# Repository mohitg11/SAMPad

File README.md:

# SAMPad

This is a custom numeric pad that is designed to be usable on the right side of the keyboard or on the left (With a mirrored layout if required).
There is a gap in the top row and the second row of 1.25U. The top row can be broken off by simply scoring the two brifges and snapping.
The bottom 5 rows can then be used in conjunction with a 60%/65% keyboard.

SAMPad stands for Sundstrand Adding Machine. David Sundstrand was the inventor of the 10-key adding machine, the layout of which is used till date on most numeric pads. This is a humble dedication to the great man.

#Features
- Open Source Design
- Fully Programmable Keys
- Numpad can be mirrored for use on the left side of the main keyboard.
- Multiple layers
- Alps/Cherry (PCB/Plate) support
- PCB mount stabs supported
- Backlight, LED on bottom for windowed keycaps
- 6 Indicator LEDs, 4 on the top row and one on either Num Lock positions (Regular and mirrored)
- 4 SMD RGB LEDs on the bottom of the PCB for under/side glow
- SMD (SOD-123) diodes only
- Individual resistors for the LEDs not required as it uses a dedicated LED driver
- Using large (0805) capacitors and resistors so it is easier to hand-solder
- Possibility to add a buzzer
- Possibility to add a rotary dial on the top-right most key position for changing volume, LED brightness, etc.

#Layout options decided/implemented:
- Standard numpad with extra row on top with a 1.25U vertical offset that matches most TKL boards.
- Possibility for upto 5*4 + 4 keys layout
- Mirrored numpad layout for use on left side of main keyboard

In the below image you can see the different options available.

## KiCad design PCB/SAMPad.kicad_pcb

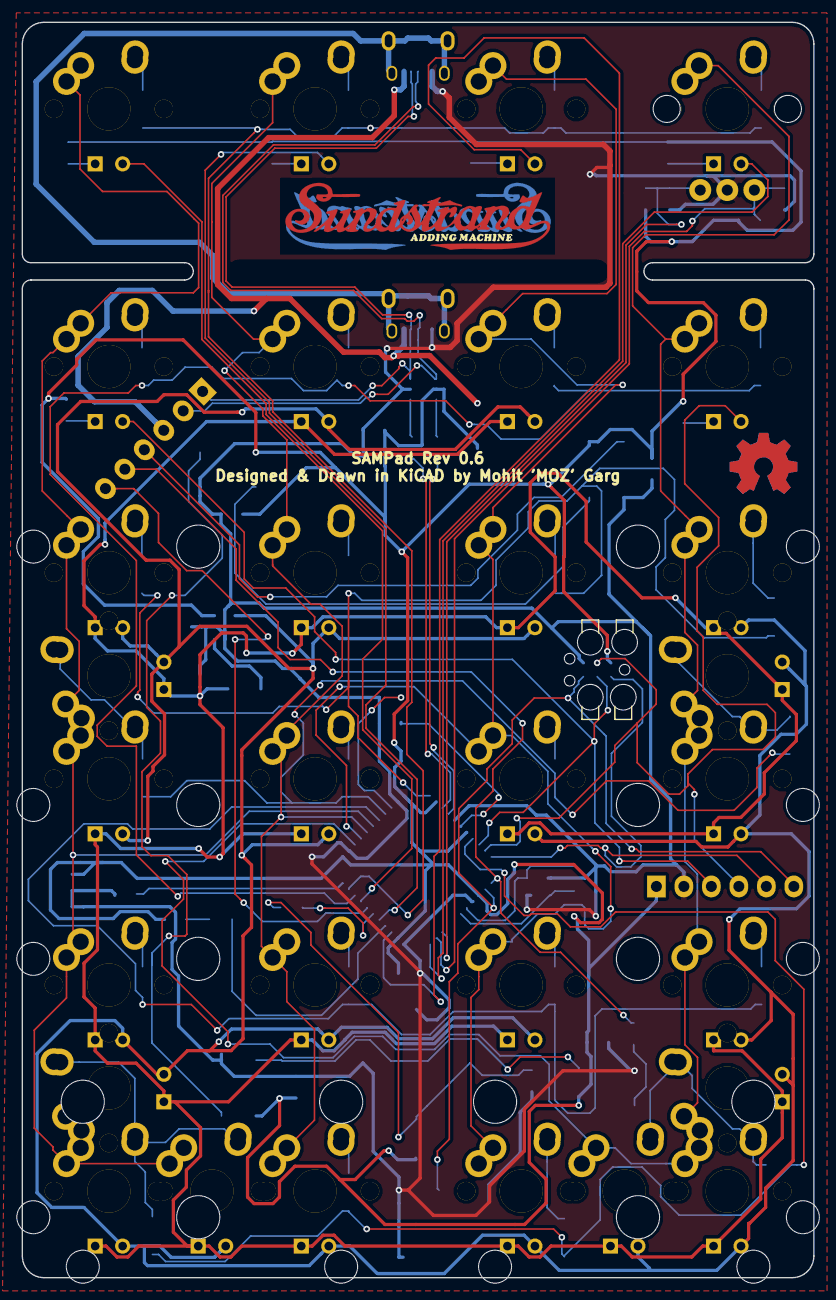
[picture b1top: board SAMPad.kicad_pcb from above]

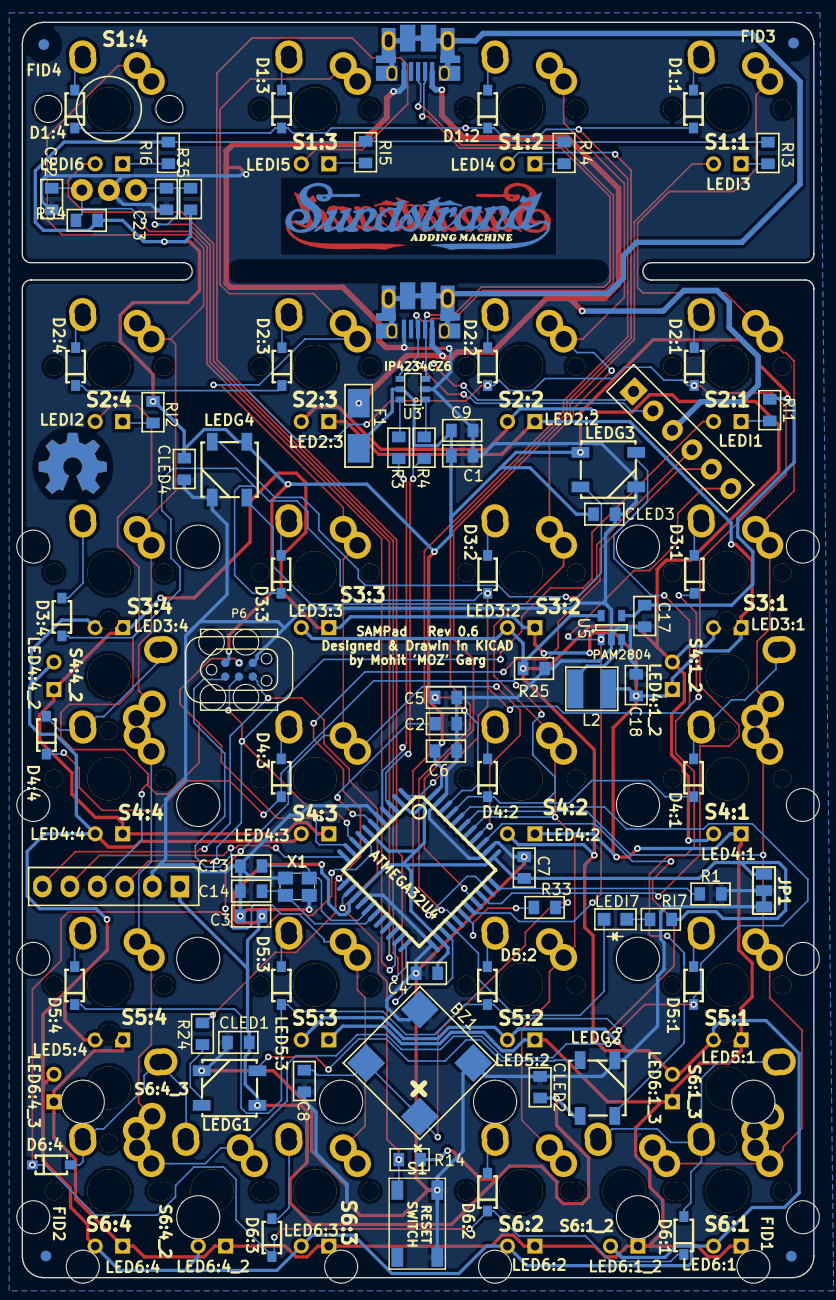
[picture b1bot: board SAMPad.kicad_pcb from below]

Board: 2 copper layers, 73.2 x 116.0 mm, 154 parts (85 on the bottom side), 79 nets.

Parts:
BZ1: BUZZER; BUZZER_SMT
C1, C2, C22, C23: 1uF; SMD_0805
C3, C4, C5, C6, C7, C8: 0.1uF; SMD_0805
C9, C17, C18: 10uF; SMD_0805
C13, C14: 8pF; SMD_0805
CLED1, CLED2, CLED3, CLED4: 0.1 uF; SMD_0805
D1:1, D1:2, D1:3, D1:4, D2:1, D2:2, D2:3, D2:4, D3:1, D3:2, D3:3, D3:4, D4:1, D4:2, D4:3, D4:4, D5:1, D5:2, D5:3, D5:4, D6:1, D6:2, D6:3, D6:4: DIODE; SOD123-DIODE
F1: PTC FUSE; Fuse_SMD1206
FID1, FID2, FID3, FID4: MISC; FID
HOLE1: MISC; FID
JP1: JUMPER; JUMPER_SMD_3
L2: 4.7uH; Inductor_Bourn_4mmx4mm
LED2:2, LED2:3, LED3:1, LED3:2, LED3:3, LED3:4, LED4:1, LED4:1_2, LED4:2, LED4:3, LED4:4, LED4:4_2, LED5:1, LED5:2, LED5:3, LED5:4, LED6:1, LED6:1_2, LED6:1_3, LED6:2, LED6:3, LED6:4, LED6:4_2, LED6:4_3: LED; INSW_LEDS_REG
LEDG1, LEDG2, LEDG3, LEDG4: WS2812B
LEDI1, LEDI2, LEDI3, LEDI4, LEDI5, LEDI6: LED; INSW_LEDS_REG
LEDI7: LED; LED_0805
LOGO1, LOGO2: MISC; SAMPad-Logo
LOGO3, LOGO4: MISC; OSHW
P1, P1_2: USB_CONN; USB_Micro-B
P4, P5: CONN_6; Pin_Header_1x06
P6: ISP6; TC2030_BIG
R1, R34, R35: 10k; SMD_0805
R3, R4: 22; SMD_0805
R14: 100k; SMD_0805
R24: 330; SMD_0805
R25: RLED; SMD_0805
R33: 100; SMD_0805
RI1, RI2, RI3, RI4, RI5, RI6, RI7: 470; SMD_0805
S1: TAC_SWITCH; TACT_5.2x5.2
S1:1, S1:2, S1:3, S1:4, S2:1, S2:2, S2:3, S2:4, S3:1, S3:2, S3:3, S3:4, S4:1, S4:1_2, S4:2, S4:3, S4:4, S4:4_2, S5:1, S5:2, S5:3, S5:4, S6:1, S6:1_2, S6:1_3, S6:2, S6:3, S6:4, S6:4_2, S6:4_3: SW; MXALPS2
S2: ENCODER; ENCODER_12MM
STAB1, STAB2, STAB3, STAB4, STAB5, STAB6: MISC; MX_200
U1: ATMEGA32U4; TQFP44
U3: IP4234CZ6; SOT457
U5: PAM2804; SOT-23-5
X1: CRYSTAL; NX3225SA

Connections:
+5V: C1.1, C3.1, C4.1, C6.1, C7.1, C9.1, C17.1, CLED1.2, CLED2.2, CLED3.1, CLED4.1, F1.2, JP1.1, LEDG1.1, LEDG2.1, LEDG3.1, LEDG4.1, P5.1, P6.2, R14.2, R34.2, R35.1, RI1.2, RI2.2, RI3.2, RI4.2, RI5.2, RI6.2, RI7.2, U1.2, U1.7, U1.14, U1.24, U1.34, U1.44, U3.5, U5.4
/ledmatrix/LEDAN: C18.1, L2.2, LED2:2.1, LED2:3.1, LED3:1.1, LED3:2.1, LED3:3.1, LED3:4.1, LED4:1.1, LED4:1_2.1, LED4:2.1, LED4:3.1, LED4:4.1, LED4:4_2.1, LED5:1.1, LED5:2.1, LED5:3.1, LED5:4.1, LED6:1.1, LED6:1_2.1, LED6:1_3.1, LED6:2.1, LED6:3.1, LED6:4.1, LED6:4_2.1, LED6:4_3.1
/ledmatrix/LEDCATH: LED2:2.2, LED2:3.2, LED3:1.2, LED3:2.2, LED3:3.2, LED3:4.2, LED4:1.2, LED4:1_2.2, LED4:2.2, LED4:3.2, LED4:4.2, LED4:4_2.2, LED5:1.2, LED5:2.2, LED5:3.2, LED5:4.2, LED6:1.2, LED6:1_2.2, LED6:1_3.2, LED6:2.2, LED6:3.2, LED6:4.2, LED6:4_2.2, LED6:4_3.2, R25.2, U5.5
/ledmatrix/LEDI1: LEDI1.2, P5.3, P6.3, U1.9
/ledmatrix/LEDI2: LEDI2.2, P5.4, P6.4, U1.10
/ledmatrix/LEDI3: LEDI3.2, U1.30
/ledmatrix/LEDI4: LEDI4.2, U1.27
/ledmatrix/LEDI5: LEDI5.2, U1.25
/ledmatrix/LEDI6: LEDI6.2, U1.22
/ledmatrix/LEDI7: LEDI7.2, U1.26
/ledmatrix/RGBDIN: P4.5, R24.2, U1.12
/ledmatrix/RGBDOUT: LEDG4.2, P4.4
/mcu/BUZZER: R33.1, U1.28
/mcu/COL1: S1:1.1, S2:1.1, S3:1.1, S4:1.1, S4:1_2.1, S5:1.1, S6:1.1, S6:1_2.1, S6:1_3.1, U1.39
/mcu/COL2: S1:2.1, S2:2.1, S3:2.1, S4:2.1, S5:2.1, S6:2.1, U1.38
/mcu/COL3: S1:3.1, S2:3.1, S3:3.1, S4:3.1, S5:3.1, S6:3.1, U1.37
/mcu/COL4: S1:4.1, S2:4.1, S3:4.1, S4:4.1, S4:4_2.1, S5:4.1, S6:4.1, S6:4_2.1, S6:4_3.1, U1.36
/mcu/D+: P1.3, P1_2.3, P4.2, U3.4
/mcu/D-: P1.2, P1_2.2, P4.1, U3.3
/mcu/ENCA: C22.1, R34.1, S2.1, U1.21
/mcu/ENCB: C23.1, R35.2, S2.3, U1.20
/mcu/HWBE: R1.2, U1.33
/mcu/LEDBL: P4.6, U1.29, U5.1
/mcu/MCURST: P5.6, P6.5, R14.1, S1.2, U1.13
/mcu/MISO: P5.5, P6.1, U1.11
/mcu/ROW1: D1:1.2, D1:2.2, D1:3.2, D1:4.2, U1.32
/mcu/ROW2: D2:1.2, D2:2.2, D2:3.2, D2:4.2, U1.31
/mcu/ROW3: D3:1.2, D3:2.2, D3:3.2, D3:4.2, U1.1
/mcu/ROW4: D4:1.2, D4:2.2, D4:3.2, D4:4.2, U1.41
/mcu/ROW5: D5:1.2, D5:2.2, D5:3.2, D5:4.2, U1.40
/mcu/ROW6: D6:1.2, D6:2.2, D6:3.2, D6:4.2, U1.8
/mcu/SHDGND: P1.6, P1_2.6
/mcu/USB_D+: R3.2, U1.4
/mcu/USB_D-: R4.2, U1.3
/mcu/VUSB: F1.1, P1.1, P1_2.1, P4.3
/mcu/XTAL1: C14.1, U1.17, X1.3
/mcu/XTAL2: C13.1, U1.16, X1.1
unnamed: BZ1.1, C8.2, R33.2
unnamed: C2.1, U1.6
unnamed: C5.1, U1.42
unnamed: D1:1.1, S1:1.2
unnamed: D1:2.1, S1:2.2
unnamed: D1:3.1, S1:3.2
unnamed: D1:4.1, S1:4.2
unnamed: D2:1.1, S2:1.2
unnamed: D2:2.1, S2:2.2
unnamed: D2:3.1, S2:3.2
unnamed: D2:4.1, S2:4.2
unnamed: D3:1.1, S3:1.2
unnamed: D3:2.1, S3:2.2
unnamed: D3:3.1, S3:3.2
unnamed: D3:4.1, S3:4.2
unnamed: D4:1.1, S4:1.2, S4:1_2.2
unnamed: D4:2.1, S4:2.2
unnamed: D4:3.1, S4:3.2
unnamed: D4:4.1, S4:4.2, S4:4_2.2
unnamed: D5:1.1, S5:1.2
unnamed: D5:2.1, S5:2.2
unnamed: D5:3.1, S5:3.2
unnamed: D5:4.1, S5:4.2
unnamed: D6:1.1, S6:1.2, S6:1_2.2, S6:1_3.2
unnamed: D6:2.1, S6:2.2
unnamed: D6:3.1, S6:3.2
unnamed: D6:4.1, S6:4.2, S6:4_2.2, S6:4_3.2
unnamed: L2.1, U5.3
unnamed: LEDG1.2, LEDG2.4
unnamed: LEDG1.4, R24.1
unnamed: LEDG2.2, LEDG3.4
unnamed: LEDG3.2, LEDG4.4
unnamed: LEDI1.1, RI1.1
unnamed: LEDI2.1, RI2.1
unnamed: LEDI3.1, RI3.1
unnamed: LEDI4.1, RI4.1
unnamed: LEDI5.1, RI5.1
unnamed: LEDI6.1, RI6.1
unnamed: LEDI7.1, RI7.1
unnamed: R3.1, U3.6
unnamed: R4.1, U3.1
VSS: BZ1.2, C1.2, C2.2, C3.2, C4.2, C5.2, C6.2, C7.2, C8.1, C9.2, C13.2, C14.2, C17.2, C18.2, C22.2, C23.2, CLED1.1, CLED2.1, CLED3.2, CLED4.2, JP1.2, JP1.3, LEDG1.3, LEDG2.3, LEDG3.3, LEDG4.3, P1.5, P1_2.5, P5.2, P6.6, R1.1, R25.1, S1.3, S1.4, S2.2, U1.5, U1.15, U1.23, U1.35, U1.43, U3.2, U5.2, X1.2, X1.4

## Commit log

2016-03-31 Fix Possible UVCC error
2016-03-31 Renders updated
2016-03-31 upload layouts
2016-04-15 Rev 0.2
2016-04-15 Minor fixes to silkscreen
2016-04-20 v0.3
2016-04-20 Rev 0.4 - Removed 3.3V regulator
2016-04-20 BOM updated to Rev 0.4
2016-04-24 Add case
2016-04-25 Removed Shottky diode
2016-04-26 Rev 0.5
2016-04-28 Minor update to correct silkscreen on Rev 0.5
2016-05-01 Minor revision update, corrected the UCAP connection on MCU
2016-05-10 Update BOM
2016-05-20 Rev 0.6
